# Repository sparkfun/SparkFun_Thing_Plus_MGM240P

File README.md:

SparkFun Thing Plus Matter - MGM240P
========================================

[*SparkFun Thing Plus Matter - MGM240P (DEV-20270)*](https://www.sparkfun.com/products/20270)

The SparkFun Thing Plus Matter - MGM240P . The MGM3240P wireless module from Silicon Labs<sup>&reg;</sup> provides secure connectivity for both 802.15.4 and Bluetooth<sup>&reg;</sup> Low Energy 5.3 protocols. The module comes ready for integration into Silicon Labs' [Matter](https://www.silabs.com/wireless/matter) IoT protocol for home automation. SparkFun's [Thing Plus](https://www.sparkfun.com/thing_plus) development boards are Feather-compatible and include a Qwiic connector for easy integration into our Qwiic Connect System for solderless I<sup>2</sup>C circuits.

The SparkFun Thing Plus Matter - MGM240P includes Qwiic and LiPo battery connectors, multiple GPIO pins capable of complete multiplexing through software. The board also features the MCP73831 single-cell LiPo charger as well as the MAX17048 fuel gauge to charge and monitor a connected battery. Lastly, we've included a &micro;SD card slot for any external memory needs.

Repository Contents
-------------------

* **/Documentation** - Data sheets, additional product information
* **/Hardware** - Eagle design files (.brd, .sch)
* **/Production** - Production panel files (.brd)

Documentation
--------------
* **[Hookup Guide](https://learn.sparkfun.com/tutorials/sparkfun-thing-plus-matter---mgm240p-hookup-guide)** - Basic hookup guide for the Thing Plus Matter - MGM240P.
* **[Fritzing Part](https://github.com/sparkfun/Fritzing_Parts/blob/main/products/20270_sfe_thing_plus_matter_mgm240p.fzpz)** -  Fritzing diagrams for SparkFun products.

Product Versions
----------------
* [DEV-20270](https://www.sparkfun.com/products/20270)- Initial release of the Thing Plus Matter - MGM240P 

License Information
-------------------

This product is _**open source**_! 

Please review the LICENSE.md file for license information. 

If you have any questions or concerns on licensing, please contact technical support on our [SparkFun forums](https://forum.sparkfun.com/viewforum.php?f=152).

Distributed as-is; no warranty is given.

- Your friends at SparkFun.

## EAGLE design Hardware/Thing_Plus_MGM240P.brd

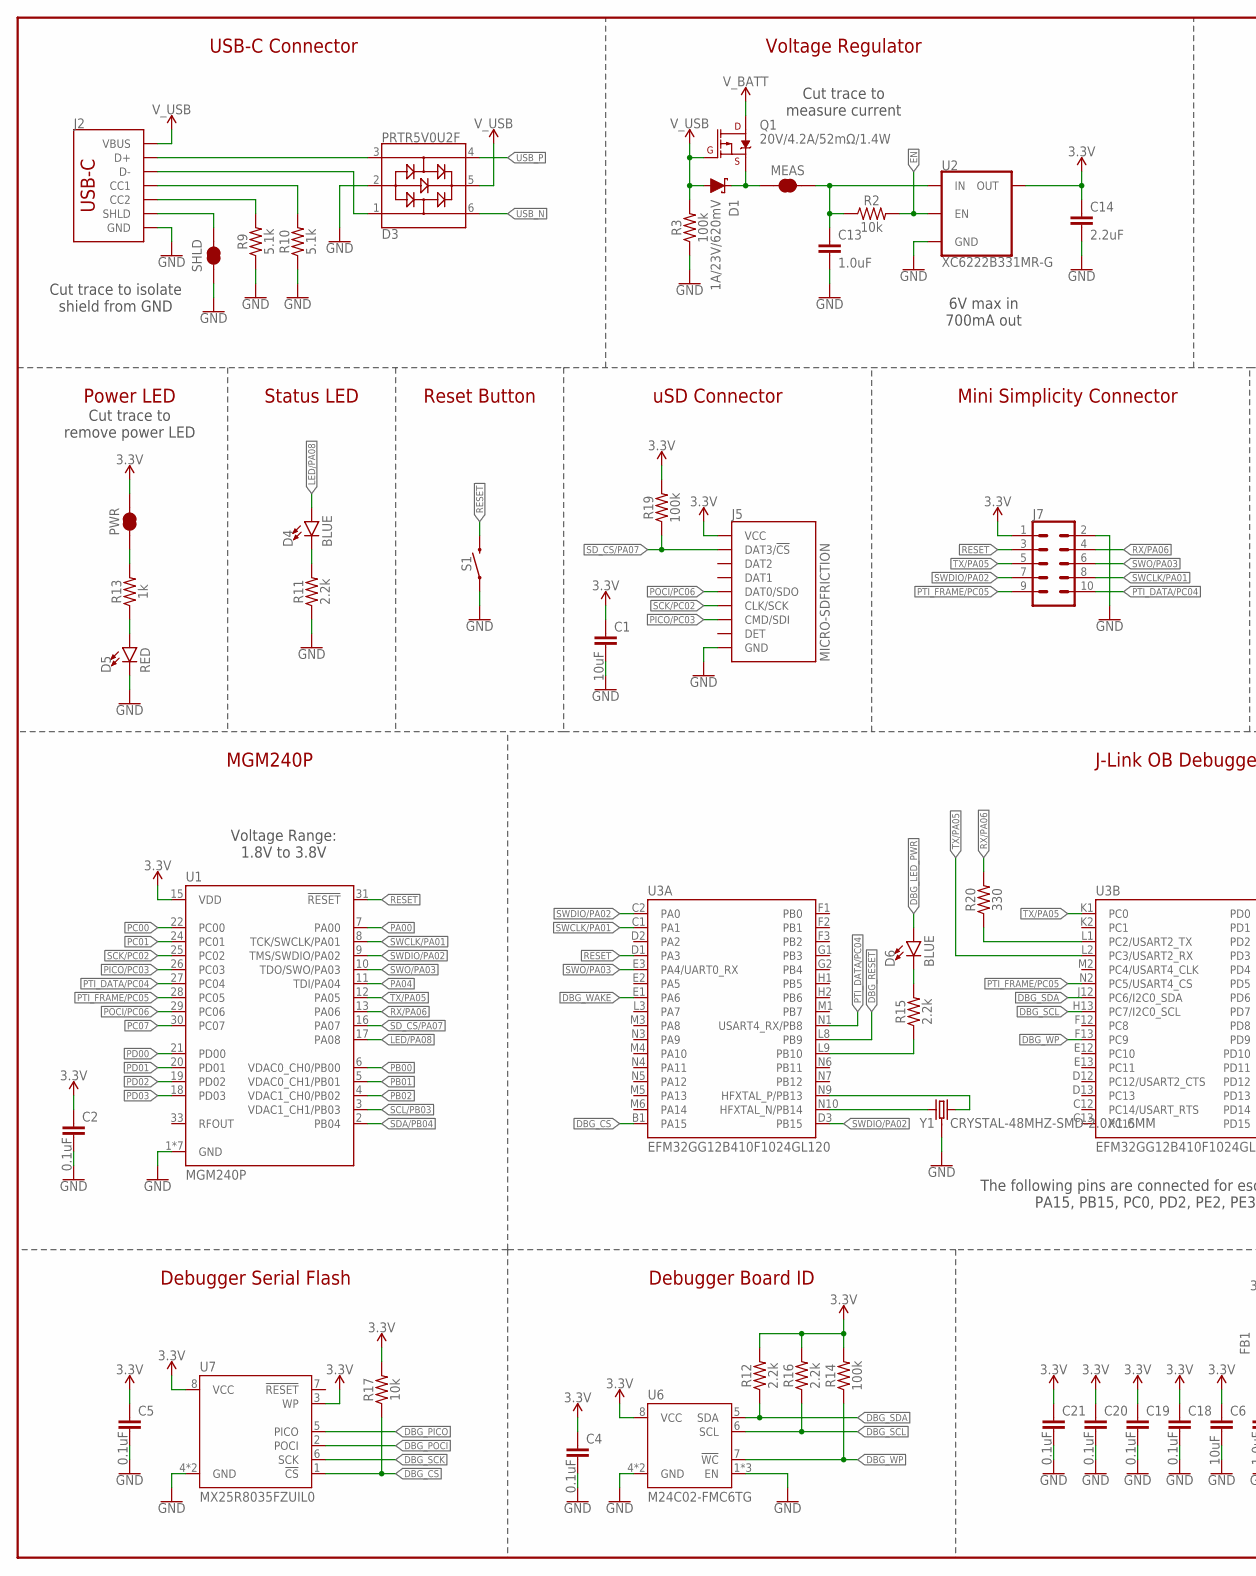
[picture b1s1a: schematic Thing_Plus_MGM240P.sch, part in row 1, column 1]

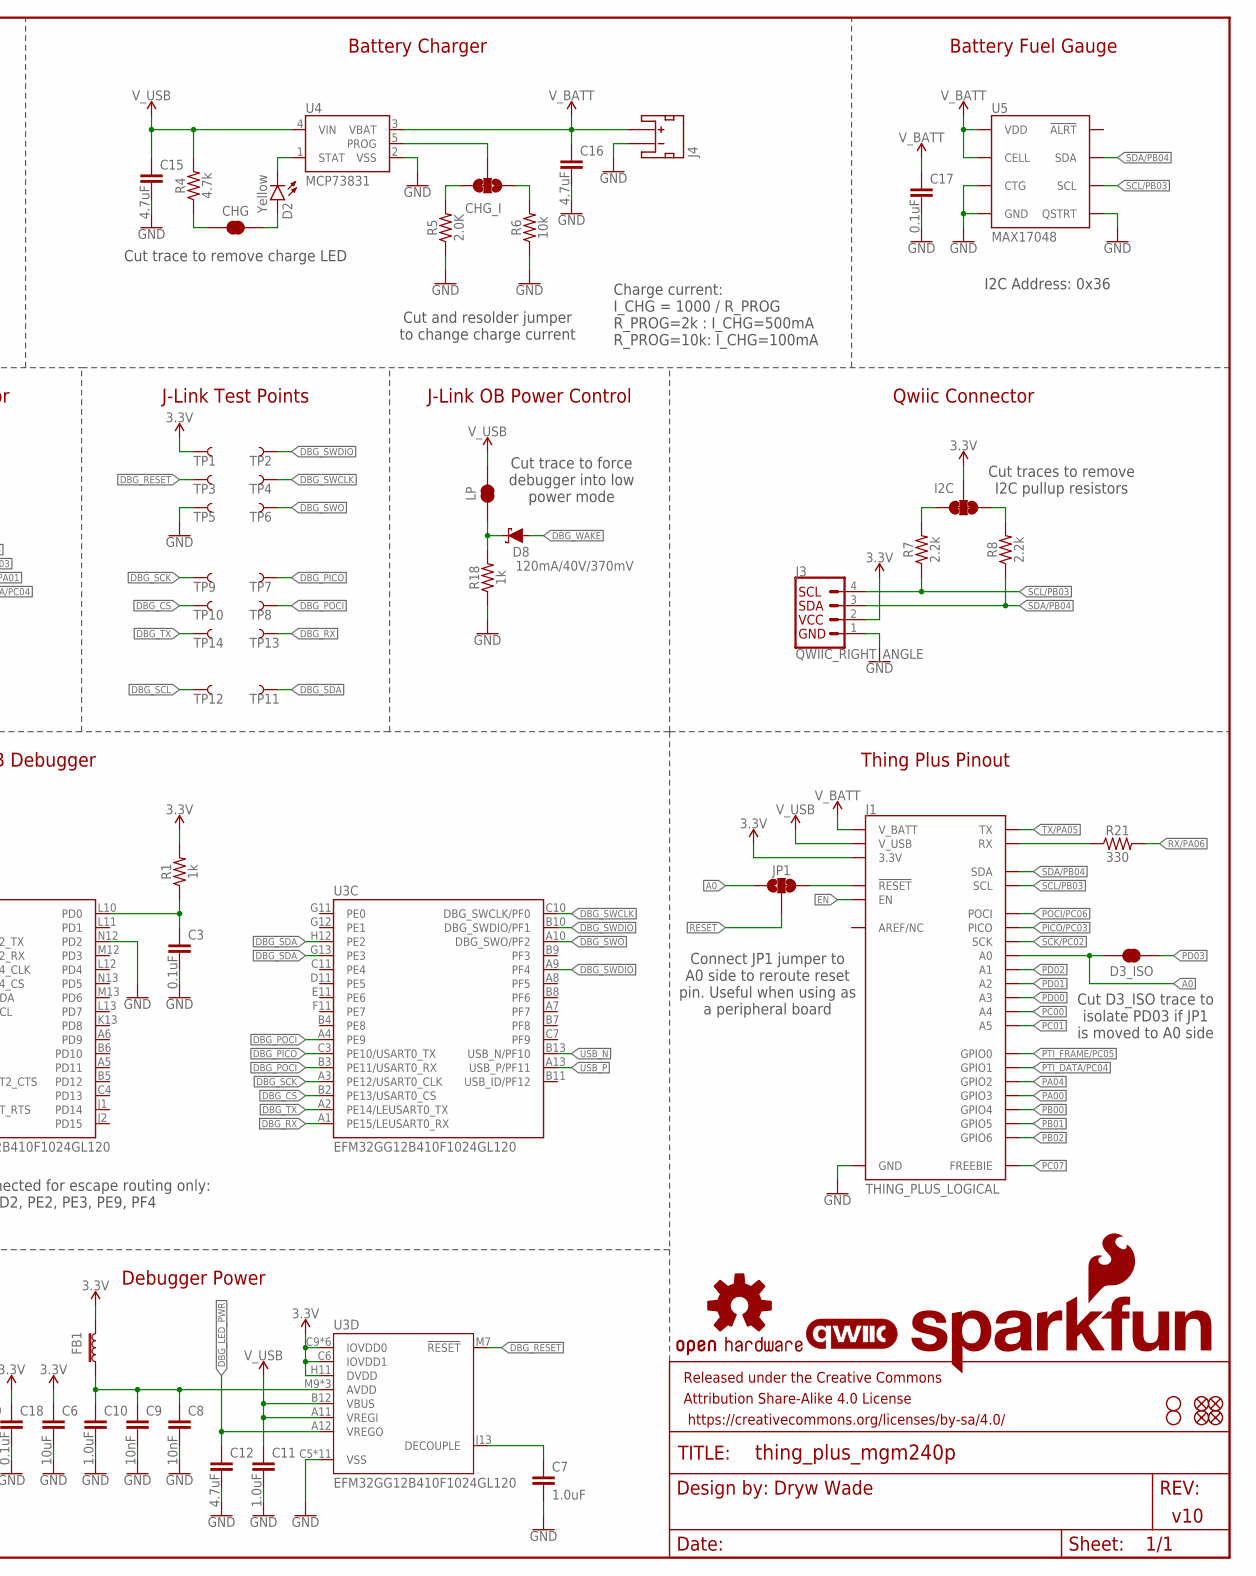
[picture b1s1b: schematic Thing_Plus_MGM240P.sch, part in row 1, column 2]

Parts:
C1, C6: 10uF; 0402-TIGHT
C2, C3, C4, C5, C17, C18, C19, C20, C21: 0.1uF; 0402-TIGHT
C7: 1.0uF; 0603
C8, C9: 10nF; 0402-TIGHT
C10, C11, C13: 1.0uF; 0402-TIGHT
C12, C15, C16: 4.7uF; 0402-TIGHT
C14: 2.2uF; 0402-TIGHT
CHG: JUMPER-SMT_2_NC_TRACE_SILK; SMT-JUMPER_2_NC_TRACE_SILK
CHG_I: JUMPER-SMT_3_1-NC_TRACE_SILK; SMT-JUMPER_3_1-NC_TRACE_SILK
D1: 1A/23V/620mV; SOD-323
D2: Yellow; LED-0603
D3: PRTR5V0U2F; SOT886
D3_ISO: JUMPER-SMT_2_NC_TRACE_SILK; SMT-JUMPER_2_NC_TRACE_SILK
D4, D6: BLUE; LED-0603
D5: RED; LED-0603
D8: 120mA/40V/370mV; SOD-523
FB1: FERRITE_BEAD-120_OHM-0402T; 0402-TIGHT
FD1, FD2, FD3, FD4: FIDUCIAL1X2; FIDUCIAL-1X2
FRAME1: FRAME-LEDGER; CREATIVE_COMMONS
H1, H2: STAND-OFF
I2C: JUMPER-SMT_3_2-NC_TRACE_SILK; SMT-JUMPER_3_2-NC_TRACE_SILK
J1: THING_PLUS_LOGICAL; THING_PLUS
J2: USB Female Type C Connector; USB-C-16P-4LAYER-ISOLATED
J3: QWIIC_RIGHT_ANGLE; JST04_1MM_RA
J4: JST_2MM_MALE; JST-2-SMD
J5: MICRO-SDFRICTION; MICROSD_TINY
J7: CONN_05X20.05_IN_PTH_SILK; 2X5_PTH_SILK_.05
JP1: JUMPER-SMT_3_1-NC_TRACE_SILK; SMT-JUMPER_3_1-NC_TRACE_SILK
LOGO1: SFE_LOGO_NAME_FLAME.1_INCH; SFE_LOGO_NAME_FLAME_.1
LOGO2: QWIIC_LOGO_3MM; QWIIC_3MM
LOGO3: OSHW-LOGOS; OSHW-LOGO-S
LP: JUMPER-SMT_2_NC_TRACE_SILK; SMT-JUMPER_2_NC_TRACE_SILK
MEAS: JUMPER-COMBO_2_NC_TRACE; COMBO-JUMPER_2_NC_TRACE
PWR: JUMPER-SMT_2_NC_TRACE_SILK; SMT-JUMPER_2_NC_TRACE_SILK
Q1: 20V/4.2A/52mΩ/1.4W; SOT23-3
R1, R13, R18: 1k; 0402-TIGHT
R2, R6, R17: 10k; 0402-TIGHT
R3, R14, R19: 100k; 0402-TIGHT
R4: 4.7k; 0402-TIGHT
R5: 2.0K; 0402-TIGHT
R7, R8, R11, R12, R15, R16: 2.2k; 0402-TIGHT
R9, R10: 5.1k; 0402-TIGHT
R20, R21: 330; 0402-TIGHT
S1: MOMENTARY-SWITCH-SPST-SMD-4.6X2.8MM; TACTILE_SWITCH_SMD_4.6X2.8MM
SHLD: JUMPER-SMT_2_NC_TRACE_SILK; SMT-JUMPER_2_NC_TRACE_SILK
TP1, TP2, TP3, TP4, TP5, TP6, TP7, TP8, TP9, TP10, TP11, TP12, TP13, TP14: TEST-POINT3; PAD.03X.03
U1: MGM240P
U2: XC6222B331MR-G; SOT23-5
U3: EFM32GG12B410F1024GL120; BGA120
U4: MCP73831; SOT23-5
U5: MAX17048; DFN-8
U6: M24C02-FMC6TG; DFN8_2X3MM
U7: MX25R8035FZUIL0; USON-8_2X3MM
Y1: CRYSTAL-48MHZ-SMD-2.0X1.6MM; CRYSTAL-SMD-2.0X1.6MM-ECS

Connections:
3.3V: C1.1, C2.1, C4.1, C5.1, C6.1, C14.1, C18.1, C19.1, C20.1, C21.1, FB1.2, I2C.2, J1.27 (3.3V), J3.2, J5.4 (VCC), J7.1, PWR.2, R1.2, R12.2, R14.2, R16.2, R17.2, R19.2, TP1.1, U1.15 (VDD), U2.5 (OUT), U3.C6 (IOVDD1), U3.C9 (IOVDD0), U3.G3 (IOVDD0), U3.H11 (DVDD), U3.J11 (IOVDD0), U3.K3 (IOVDD0), U3.L4 (IOVDD0), U3.L7 (IOVDD0), U6.8 (VCC), U7.3 (WP), U7.8 (VCC)
!DBG_RESET!: TP3.1, U3.L8 (PB9), U3.M7 (!RESET!)
!RESET!: J7.3, JP1.2, S1.3 (2), S1.4 (2), U1.31 (!RESET!), U3.D1 (PA3)
!SD_CS!/PA07: J5.2 (DAT3/!CS!), R19.1, U1.16 (PA07)
A0: D3_ISO.2, J1.24 (A0), JP1.1
DBG_CS: R17.1, TP10.1, U3.B1 (PA15), U3.B2 (PE13/USART0_CS), U7.1 (!CS!)
DBG_LED_PWR: C12.1, D6.A, U3.A12 (VREGO)
DBG_PICO: TP7.1, U3.C3 (PE10/USART0_TX), U7.5 (PICO)
DBG_POCI: TP8.1, U3.A4 (PE9), U3.B3 (PE11/USART0_RX), U7.2 (POCI)
DBG_RX: TP13.1, U3.A1 (PE15/LEUSART0_RX)
DBG_SCK: TP9.1, U3.A3 (PE12/USART0_CLK), U7.6 (SCK)
DBG_SCL: R16.1, TP12.1, U3.H13 (PC7/I2C0_SCL), U6.6 (SCL)
DBG_SDA: R12.1, TP11.1, U3.G13 (PE3), U3.H12 (PE2), U3.J12 (PC6/I2C0_SDA), U6.5 (SDA)
DBG_SWCLK: TP4.1, U3.C10 (DBG_SWCLK/PF0)
DBG_SWDIO: TP2.1, U3.A9 (PF4), U3.B10 (DBG_SWDIO/PF1)
DBG_SWO: TP6.1, U3.A10 (DBG_SWO/PF2)
DBG_TX: TP14.1, U3.A2 (PE14/LEUSART0_TX)
DBG_WAKE: D8.A, U3.E1 (PA6)
DBG_WP: R14.1, U3.F13 (PC9), U6.7 (!WC!)
EN: J1.11 (EN), R2.2, U2.3 (EN)
GND: C1.2, C2.2, C3.2, C4.2, C5.2, C6.2, C7.2, C8.2, C9.2, C10.2, C11.2, C12.2, C13.2, C14.2, C15.2, C16.2, C17.2, C18.2, C19.2, C20.2, C21.2, D3.2, D5.C, J1.25 (GND), J2.GND, J2.GND2 (GND), J3.1, J4.1 (-), J5.6 (GND), J5.GND1 (GND), J5.GND2 (GND), J5.GND3 (GND), J5.GND4 (GND), J5.GND5 (GND), J5.GND6 (GND), J7.2, R3.1, R5.1, R6.1, R9.1, R10.1, R11.1, R18.1, S1.1, S1.2 (1), SHLD.1, TP5.1, U1.1 (GND), U1.14 (GND), U1.23 (GND), U1.32 (GND), U1.34 (GND), U1.35 (GND), U1.36 (GND), U2.2 (GND), U3.C5 (VSS), U3.C8 (VSS), U3.H3 (VSS), U3.J3 (VSS), U3.K11 (VSS), U3.K12 (VSS), U3.L5 (VSS), U3.L6 (VSS), U3.M8 (VSS), U3.M11 (VSS), U3.N8 (VSS), U3.N12 (PD2), U4.2 (VSS), U5.1 (CTG), U5.4 (GND), U5.6 (QSTRT), U5.9 (GND), U6.1 (EN), U6.2 (EN), U6.3 (EN), U6.4 (GND), U6.EPAD (GND), U7.4 (GND), U7.EPAD (GND), Y1.2 (GND), Y1.4 (GND)
LED/PA08: D4.A, U1.17 (PA08)
unnamed: D4.C, R11.2
unnamed: PWR.1, R13.2
unnamed: CHG.2, D2.A
unnamed: CHG_I.1, R6.2
unnamed: D2.C, U4.1 (STAT)
unnamed: CHG_I.3, R5.2
unnamed: D1.C, MEAS.1, MEAS.3 (1), Q1.2 (S)
unnamed: D5.A, R13.1
unnamed: CHG_I.2, U4.5 (PROG)
unnamed: CHG.1, R4.1
unnamed: I2C.3, R7.2
unnamed: C3.1, R1.1, U3.L10 (PD0)
unnamed: I2C.1, R8.2
unnamed: J2.B5 (CC2), R9.2
unnamed: J2.A5 (CC1), R10.2
unnamed: D3.3, J2.A6 (D+), J2.B6 (D+)
unnamed: C7.1, U3.J13 (DECOUPLE)
unnamed: D3.1, J2.A7 (D-), J2.B7 (D-)
unnamed: C8.1, C9.1, C10.1, FB1.1, U3.M9 (AVDD), U3.M10 (AVDD), U3.N11 (AVDD)
unnamed: R15.1, U3.L9 (PB10)
unnamed: D6.C, R15.2
unnamed: U3.N10 (HFXTAL_N/PB14), Y1.1
unnamed: U3.N9 (HFXTAL_P/PB13), Y1.3 (2)
unnamed: D8.C, LP.1, R18.2
unnamed: R20.1, U3.L1 (PC2/USART2_TX)
unnamed: J1.15 (RX), R21.1
unnamed: C13.1, MEAS.2, MEAS.4 (2), R2.1, U2.1 (IN)
unnamed: J1.28 (!RESET), JP1.3
PA00: J1.6 (GPIO3), U1.7 (PA00)
PA04: J1.7 (GPIO2), U1.11 (TDI/PA04)
PB00: J1.5 (GPIO4), U1.6 (VDAC0_CH0/PB00)
PB01: J1.4 (GPIO5), U1.5 (VDAC0_CH1/PB01)
PB02: J1.3 (GPIO6), U1.4 (VDAC1_CH0/PB02)
PC00: J1.20 (A4), U1.22 (PC00)
PC01: J1.19 (A5), U1.24 (PC01)
PC07: J1.13 (FREEBIE), U1.30 (PC07)
PD00: J1.21 (A3), U1.21 (PD00)
PD01: J1.22 (A2), U1.20 (PD01)
PD02: J1.23 (A1), U1.19 (PD02)
PD03: D3_ISO.1, U1.18 (PD03)
PICO/PC03: J1.17 (PICO), J5.3 (CMD/SDI), U1.26 (PC03)
POCI/PC06: J1.16 (POCI), J5.7 (DAT0/SDO), U1.29 (PC06)
PTI_DATA/PC04: J1.8 (GPIO1), J7.10, U1.27 (PC04), U3.N1 (USART4_RX/PB8)
PTI_FRAME/PC05: J1.9 (GPIO0), J7.9, U1.28 (PC05), U3.N2 (PC5/USART4_CS)
RX/PA06: J7.4, R20.2, R21.2, U1.13 (PA06)
SCK/PC02: J1.18 (SCK), J5.5 (CLK/SCK), U1.25 (PC02)
SCL/PB03: J1.2 (SCL), J3.4, R7.1, U1.3 (VDAC1_CH1/PB03), U5.7 (SCL)
SDA/PB04: J1.1 (SDA), J3.3, R8.1, U1.2 (PB04), U5.8 (SDA)
SHLD: J2.SHLD1 (SHLD), J2.SHLD2 (SHLD), J2.SHLD3 (SHLD), J2.SHLD4 (SHLD), J2.SHLD5 (SHLD), J2.SHLD6 (SHLD), J2.SHLD7 (SHLD), J2.SHLD8 (SHLD), SHLD.2
SWCLK/PA01: J7.8, U1.8 (TCK/SWCLK/PA01), U3.C1 (PA1)
SWDIO/PA02: J7.7, U1.9 (TMS/SWDIO/PA02), U3.C2 (PA0), U3.D3 (PB15)
SWO/PA03: J7.6, U1.10 (TDO/SWO/PA03), U3.E3 (PA4/UART0_RX)
TX/PA05: J1.14 (TX), J7.5, U1.12 (PA05), U3.K1 (PC0), U3.L2 (PC3/USART2_RX)
USB_N: D3.6, U3.B13 (USB_N/PF10)
USB_P: D3.4, U3.A13 (USB_P/PF11)
V_BATT: C16.1, C17.1, J1.12 (V_BATT), J4.2 (+), Q1.3 (D), U4.3 (VBAT), U5.2 (CELL), U5.3 (VDD)
V_USB: C11.1, C15.1, D1.A, D3.5, J1.10 (V_USB), J2.VBUS1 (VBUS), J2.VBUS2 (VBUS), LP.2, Q1.1 (G), R3.2, R4.2, U3.A11 (VREGI), U3.B12 (VBUS), U4.4 (VIN)

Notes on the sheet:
Voltage Regulator
Battery Charger
Battery Fuel Gauge
USB-C Connector
I2C Address: 0x36
Cut trace to remove charge LED
Charge current: I_CHG = 1000 / R_PROG R_PROG=2k : I_CHG=500mA R_PROG=10k: I_CHG=100mA
Cut and resolder jumper to change charge current
6V max in 700mA out
Cut trace to isolate shield from GND
Cut trace to measure current
Qwiic Connector
uSD Connector
Cut traces to remove I2C pullup resistors
Mini Simplicity Connector
Status LED
J-Link Test Points
J-Link OB Debugger
Thing Plus Pinout
MGM240P
J-Link OB Power Control
Dryw Wade
v10
Cut trace to remove power LED
Reset Button
Power LED
Voltage Range: 1.8V to 3.8V
Debugger Serial Flash
Debugger Board ID
Debugger Power
Cut trace to force debugger into low power mode
Connect JP1 jumper to A0 side to reroute reset pin. Useful when using as a peripheral board
Cut D3_ISO trace to isolate PD03 if JP1 is moved to A0 side
The following pins are connected for escape routing only: PA15, PB15, PC0, PD2, PE2, PE3, PE9, PF4

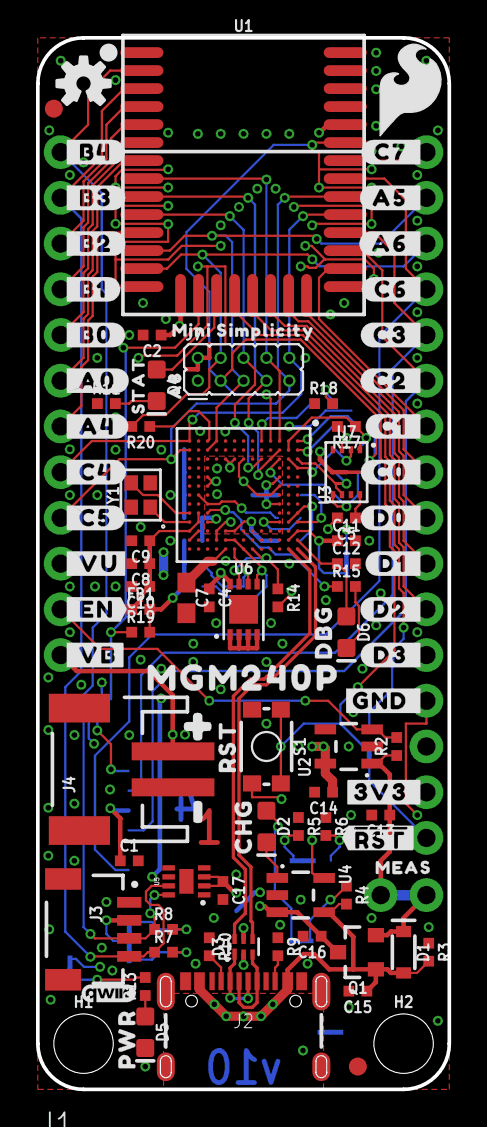
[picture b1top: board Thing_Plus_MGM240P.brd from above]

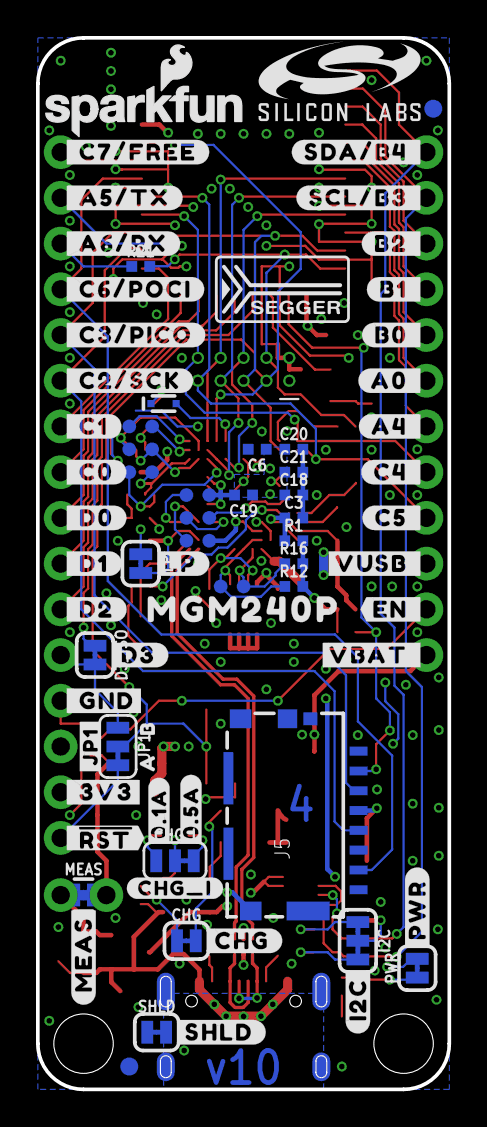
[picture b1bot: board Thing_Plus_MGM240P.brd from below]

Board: 4 copper layers, 22.9 x 58.4 mm, 182 parts (80 on the bottom side), 79 nets.

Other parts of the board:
U$1: #_B4#0
U$2: #_B3#0
U$3: #_B2#0
U$4: #_B1#0
U$5: #SHLD#0
U$6: #_B0#0
U$7: #_A0#0
U$8: #_A4#0
U$9: #_C5#0
U$10: #_C4#0
U$11: #C7_#0
U$12: #A5_#0
U$13: #A6_#0
U$14: #C6_#0
U$15: #C3_#0
U$16: #C2_#0
U$17: #C1_#0
U$18: #C0_#0
U$19: #PWR#0
U$20: PWR0
U$21: #GND_#0
U$22: #3V3_#0
U$23, U$58: MGM240P0
U$24: #D0_#0
U$25: #_VB#0
U$26: #_VU#0
U$27: #_EN#0
U$28: ##RST##0
U$29: SFE_LOGO_FLAME_.2
U$30: #0
U$31: #1
U$32: #D1_#0
U$33: #LP#0
U$34: #_A6#RX#0
U$35: #_C6#POCI#0
U$36: #_C3#PICO#0
U$37: #_C2#SCK#0
U$38: MINI_SIMPLICITY0
U$39: #_C1#0
U$40: #_C0#0
U$41: #_D0#0
U$42: #_D1#0
U$43: #_GND#0
U$44: #_3V3#0
U$45: #_#RST##0
U$46: #_D2#0
U$47: SEGGER_LOGO_7.5MM
U$48: #C4_#0
U$49: #C5_#0
U$50: #A4_#0
U$51: #A0_#0
U$52: #B0_#0
U$53: #B2_#0
U$54: #B1_#0
U$55: #VBAT_#0
U$56: #VUSB_#0
U$57: #EN_#0
U$59: #MEAS#0
U$60: #CHG#0
U$61: #I2C#0
U$62: #D2_#0
U$63: #0#5A#0
U$64: #0#1A#0
U$66: MEAS81
U$67: CHG0
U$68: STAT0
U$69: #JP1#0
U$70: RST0
U$71: #_A5#TX#0
U$72: A80
U$73: #SDA#B4_#0
U$74: #SCL#B3_#0
U$75: ORDERING_INSTRUCTIONS
U$76: FOUR_LAYER_WARNING
U$77: #D3_#0
U$78: DBG0
U$79: #_C7#FREE#0
U$80: A0
U$81: B0
U$82: #D3#4
U$83: #CHG_I#0
U$84: SILICON_LABS_LOGO_9MM

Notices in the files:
parts and their libraries:
SparkFun-Aesthetics: Licensing: Creative Commons ShareAlike 4.0 International - https://creativecommons.org/licenses/by-sa/4.0
SparkFun-Aesthetics: Released under the Creative Commons Attribution Share-Alike 4.0 License
SparkFun-Aesthetics: https://creativecommons.org/licenses/by-sa/4.0
